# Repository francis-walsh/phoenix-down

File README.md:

# phoenix-down

Phoenix Down is a PWM-controlled hot plate that regulates the temperature of your morning coffee. A 12V 2A voltage source is regulated by a buck converter to deliver a maximum of 24W to the array of power resistors, heating the board to a specified temperature monitored by a thermistor. The design uses a schmitt trigger, astable multivibrator, and a thermistor to configure the duty cycle of the PWM.

The computer has population options for different thermistors and voltage references for configuring the thermistor voltage threshold.

Rev 1 schematic

Rev 1 TLspice simulation

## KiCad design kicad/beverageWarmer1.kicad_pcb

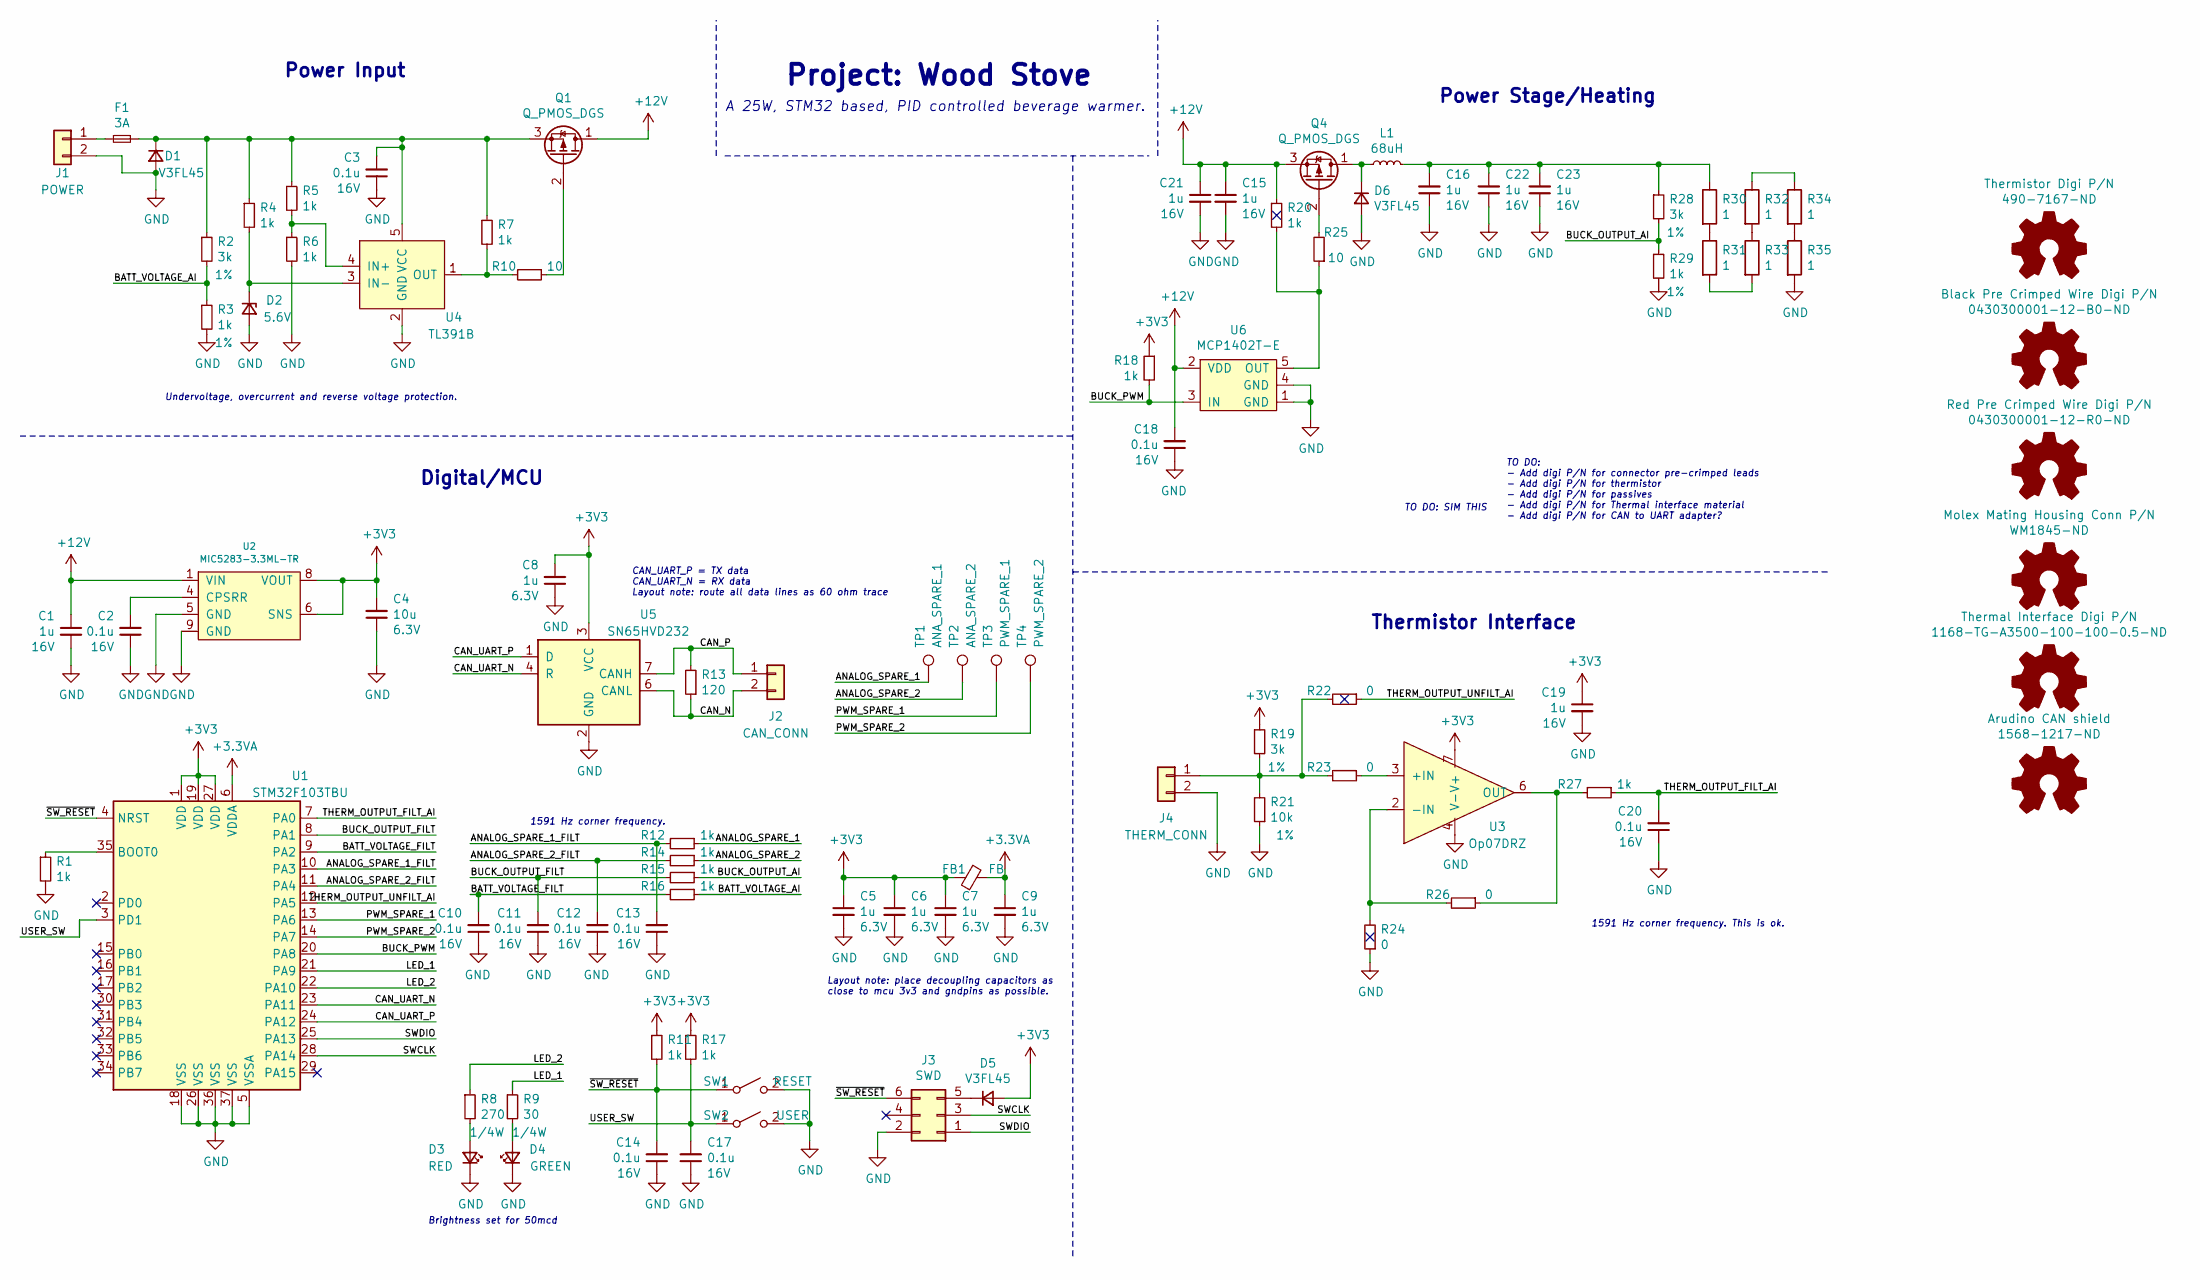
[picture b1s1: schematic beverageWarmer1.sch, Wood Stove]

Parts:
C1, C15, C16, C19, C21, C22, C23: 1u; C_0603_1608Metric; Voltage 16V; Digi 445-6931-1-ND
C2, C3, C10, C11, C12, C13, C14, C17, C18, C20: 0.1u; C_0603_1608Metric; Voltage 16V; Digi 1276-1019-1-ND
C4: 10u; C_1206_3216Metric; Voltage 6.3V; Digi 1276-6641-1-ND
C5, C6, C7, C8, C9: 1u; C_0603_1608Metric; Voltage 6.3V
D1, D5, D6: V3FL45; D_SMF; Digi V3FL45HM3/HGICT-ND
D2: 5.6V; D_SOD-123; Digi DDZ5V6BDICT-ND
D3: RED; LED_0603_1608Metric; Digi 754-1123-1-ND
D4: GREEN; LED_0603_1608Metric; Digi 754-1357-1-ND
F1: 3A; Fuse_0603_1608Metric; Digi P15118CT-ND
FB1: FB; L_0603_1608Metric; Digi 490-1015-1-ND
J1: POWER; Molex_Micro-Fit_3.0_43650-0200_1x02_P3.00mm_Horizontal; Digi WM1860-ND
J2: CAN_CONN; Molex_Micro-Fit_3.0_43650-0200_1x02_P3.00mm_Horizontal; Digi WM1860-ND
J3: SWD; PinSocket_2x03_P1.27mm_Vertical; Digi S9015E-03-ND
J4: THERM_CONN; Molex_Micro-Fit_3.0_43650-0200_1x02_P3.00mm_Horizontal; Digi WM1860-ND
L1: 68uH; L_Bourns_SRR1260; Digi SRR1260-560MCT-ND
Q1, Q4: Q_PMOS_DGS; SISS05DN-T1-GE3; Digi SISS05DN-T1-GE3CT-ND
R1, R4, R5, R6, R7, R11, R12, R14, R15, R16, R17, R18, R20, R27: 1k; R_0603_1608Metric; Digi RMCF0603JJ1K00CT-ND
R2, R19, R28: 3k; R_0603_1608Metric; Tolerance 1%; Digi RMCF0603FT3K00CT-ND
R3, R29: 1k; R_0603_1608Metric; Tolerance 1%; Digi RMCF0603FT1K00CT-ND
R8: 270; R_0805_2012Metric; Digi A130470CT-ND
R9: 30; R_0805_2012Metric; Digi 2019-RK73H2ATTD30R0FCT-ND
R10, R25: 10; R_0603_1608Metric; Digi A130079CT-ND
R13: 120; R_0603_1608Metric; Digi A129677CT-ND
R21: 10k; R_0603_1608Metric; Tolerance 1%; Digi RMCF0603FT1K00CT-ND
R22, R23, R24, R26: 0; R_0603_1608Metric; Digi 2019-RK73Z1JTTDCT-ND
R30, R32, R33, R34, R35: 1; 4320_SMD_RES; Digikey A143800CT-ND
R31: 1; 4320_SMD_RES; Digi A143800CT-ND
SW1: RESET; SW_SPST_B3U-1000P; Digi SW1020CT-ND
SW2: USER; SW_SPST_B3U-1000P; Digi SW1020CT-ND
TP1: ANA_SPARE_1; TestPoint_Pad_D1.0mm
TP2: ANA_SPARE_2; TestPoint_Pad_D1.0mm
TP3: PWM_SPARE_1; TestPoint_Pad_D1.0mm
TP4: PWM_SPARE_2; TestPoint_Pad_D1.0mm
U1: STM32F103TBU; QFN-36-1EP_6x6mm_P0.5mm_EP4.1x4.1mm; Digi 497-18758-1-ND
U2: MIC5283-3.3ML-TR; DFN-8-1EP_3x3mm_P0.65mm_EP1.55x2.4mm; Digi MIC5283-3.3YML-CT-ND
U3: Op07DRZ; SOIC-8_3.9x4.9mm_P1.27mm; Digikey OP07DRZ-ND
U4: TL391B; SOT-23-5; Digi 296-TL391BIDBVRCT-ND
U5: SN65HVD232; SOIC-8_3.9x4.9mm_P1.27mm; Digi 296-12282-5-ND
U6: MCP1402T-E; SOT-23-5; Digi MCP1402T-E/OTCT-ND

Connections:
+3.3VA: C9.1, FB1.1, U1.6 (VDDA)
+3V3: C4.2, C5.1, C6.1, C7.1, C8.2, C19.1, D5.2 (A), FB1.2, R11.1, R17.1, R18.1, R19.1, U1.1 (VDD), U1.19 (VDD), U1.27 (VDD), U2.6 (SNS), U2.8 (VOUT), U3.7 (V+), U5.3 (VCC)
+12V: C1.1, C15.1, C18.2, C21.1, Q1.1 (D), Q4.3 (S), R20.1, U2.1 (VIN), U6.2 (VDD)
/ANALOG_SPARE_1: R12.1, TP1.1
/ANALOG_SPARE_1_FILT: C13.2, R12.2, U1.10 (PA3)
/ANALOG_SPARE_2: R14.1, TP2.1
/ANALOG_SPARE_2_FILT: C12.2, R14.2, U1.11 (PA4)
/BATT_VOLTAGE_AI: R2.2, R3.1, R16.1
/BATT_VOLTAGE_FILT: C10.2, R16.2, U1.9 (PA2)
/BUCK_OUTPUT_AI: R15.1, R28.2, R29.1
/BUCK_OUTPUT_FILT: C11.2, R15.2, U1.8 (PA1)
/BUCK_PWM: R18.2, U1.20 (PA8), U6.3 (IN)
/CAN_N: J2.2, R13.1, U5.6 (CANL); also elsewhere on the board
/CAN_P: J2.1, R13.2, U5.7 (CANH); also elsewhere on the board
/CAN_UART_N: U1.23 (PA11), U5.4 (R)
/CAN_UART_P: U1.24 (PA12), U5.1 (D)
/LED_1: R9.1, U1.21 (PA9)
/LED_2: R8.1, U1.22 (PA10)
/PWM_SPARE_1: TP3.1, U1.13 (PA6)
/PWM_SPARE_2: TP4.1, U1.14 (PA7)
/SWCLK: J3.3, U1.28 (PA14); also elsewhere on the board
/SWDIO: J3.1, U1.25 (PA13); also elsewhere on the board
/THERM_OUTPUT_FILT_AI: C20.2, R27.1, U1.7 (PA0)
/THERM_OUTPUT_UNFILT_AI: R22.1, U1.12 (PA5)
/USER_SW: C17.2, R17.2, SW2.1 (A), U1.3 (PD1); also elsewhere on the board
/~SW_RESET: C14.2, J3.6, R11.2, SW1.1 (A), U1.4 (NRST); also elsewhere on the board
GND: C1.2, C2.1, C3.1, C4.1, C5.2, C6.2, C7.2, C8.1, C9.2, C10.1, C11.1, C12.1, C13.1, C14.1, C15.2, C16.1, C17.1, C18.1, C19.2, C20.1, C21.2, C22.1, C23.1, D1.2 (A), D2.2 (A), D3.1 (K), D4.1 (K), D6.2 (A), J1.2, J3.2, J4.2, R1.2, R3.2, R6.2, R21.1, R24.1, R29.2, R35.2, SW1.2 (B), SW2.2 (B), U1.5 (VSSA), U1.18 (VSS), U1.26 (VSS), U1.36 (VSS), U1.37 (VSS), U2.5 (GND), U2.9 (GND), U3.4 (V-), U4.2 (GND), U5.2 (GND), U6.1 (GND), U6.4 (GND); also elsewhere on the board
unnamed: C2.2, U2.4 (CPSRR)
unnamed: C3.2, D1.1 (K), F1.2, Q1.3 (S), R2.1, R4.1, R5.1, R7.1, U4.5 (VCC)
unnamed: C16.2, C22.2, C23.2, L1.2, R28.1, R30.1
unnamed: D2.1 (K), R4.2, U4.3 (IN-)
unnamed: D3.2 (A), R8.2
unnamed: D4.2 (A), R9.2
unnamed 33: D5.1 (K), J3.5; also elsewhere on the board
unnamed: D6.1 (K), L1.1, Q4.1 (D)
unnamed 35: F1.1, J1.1; also elsewhere on the board
unnamed 37: J4.1, R19.2, R21.2, R22.2, R23.2; also elsewhere on the board
unnamed: Q1.2 (G), R10.1
unnamed: Q4.2 (G), R25.2
unnamed: R1.1, U1.35 (BOOT0)
unnamed: R5.2, R6.1, U4.4 (IN+)
unnamed: R7.2, R10.2, U4.1 (OUT)
unnamed: R20.2, R25.1, U6.5 (OUT)
unnamed: R23.1, U3.3 (+IN)
unnamed: R24.2, R26.2, U3.2 (-IN)
unnamed: R26.1, R27.2, U3.6 (OUT)
unnamed: R30.2, R31.1
unnamed: R31.2, R33.2
unnamed: R32.1, R34.1
unnamed: R32.2, R33.1
unnamed: R34.2, R35.1

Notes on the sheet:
Layout note: place decoupling capacitors as close to mcu 3v3 and gndpins as possible.
TO DO: SIM THIS
1591 Hz corner frequency. This is ok.
Undervoltage, overcurrent and reverse voltage protection.
Thermistor Interface
Digital/MCU
Power Input
Power Stage/Heating
Project: Wood Stove
A 25W, STM32 based, PID controlled beverage warmer.
CAN_UART_P = TX data CAN_UART_N = RX data Layout note: route all data lines as 60 ohm trace
TO DO: - Add digi P/N for connector pre-crimped leads - Add digi P/N for thermistor - Add digi P/N for passives - Add digi P/N for Thermal interface material - Add digi P/N for CAN to UART adapter?
1591 Hz corner frequency.
Brightness set for 50mcd

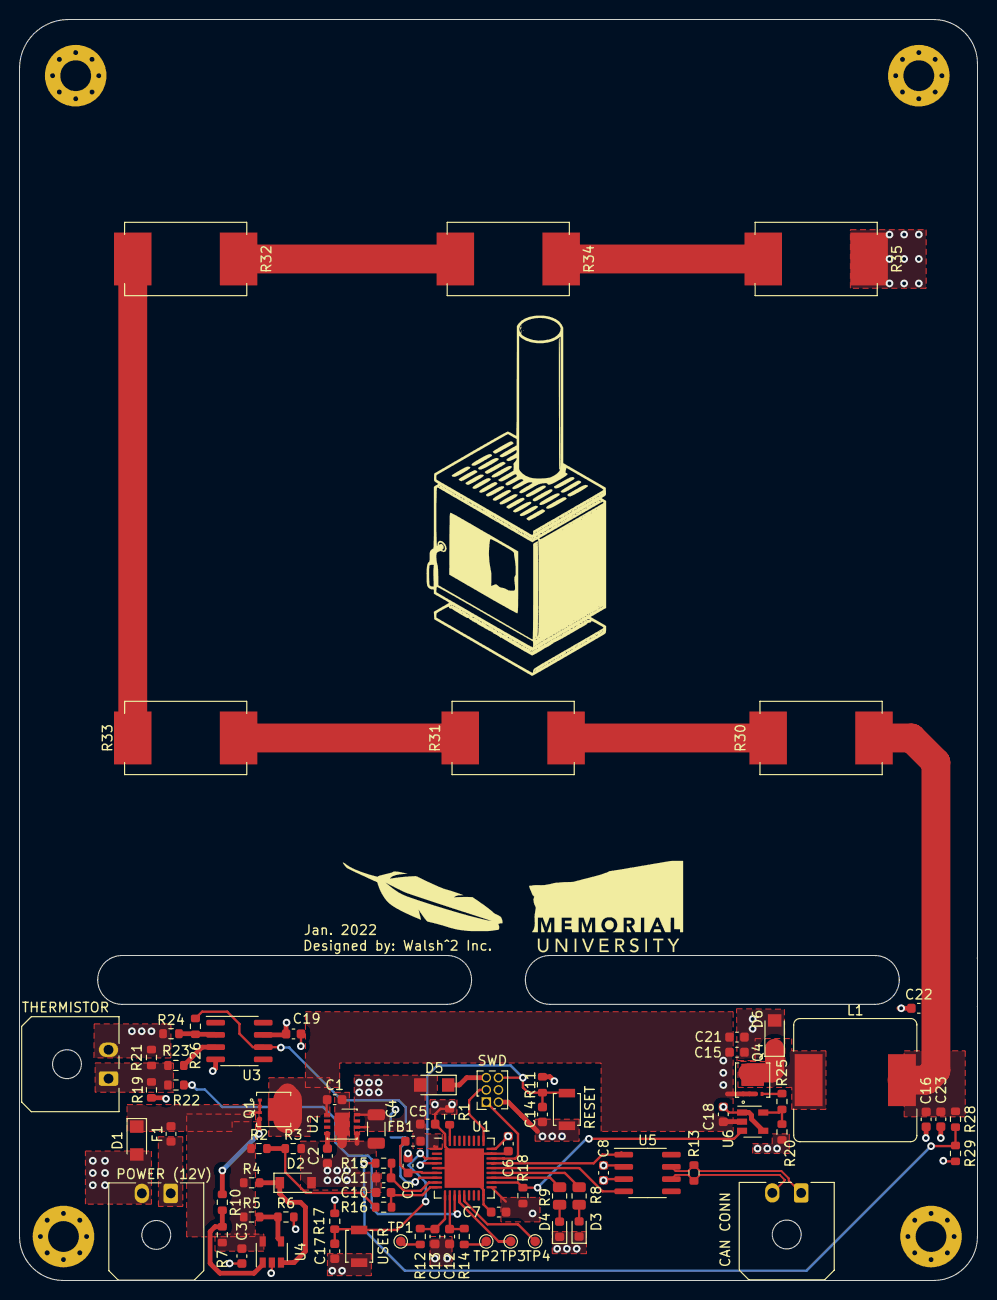
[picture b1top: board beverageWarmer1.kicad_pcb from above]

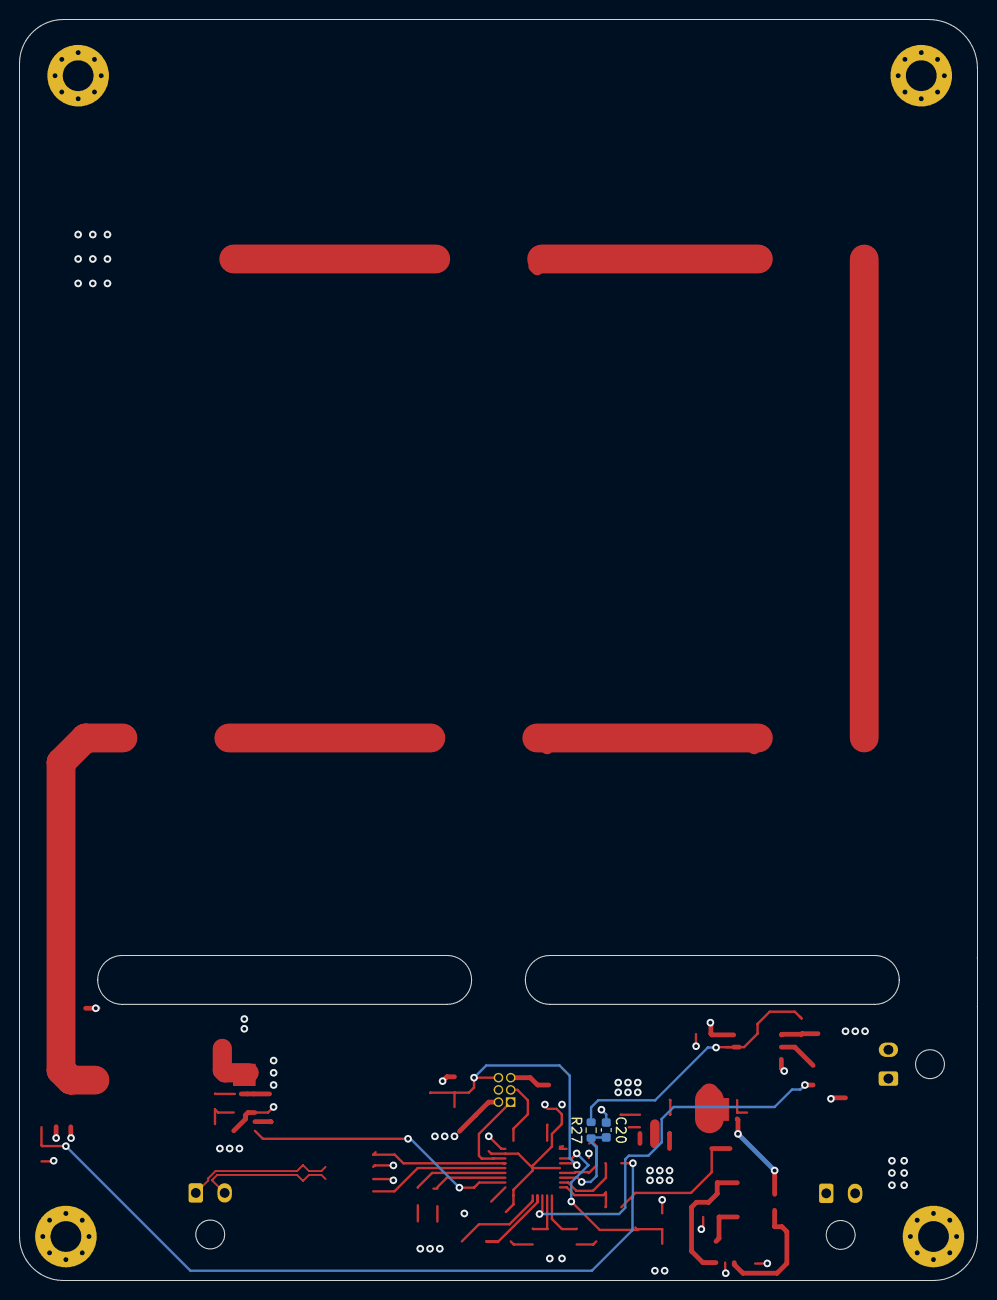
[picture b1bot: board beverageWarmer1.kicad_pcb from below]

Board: 4 copper layers, 99.6 x 131.1 mm, 85 parts (2 on the bottom side), 51 nets.

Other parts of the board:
CAN CONN: CAN_CONN; Molex_Micro-Fit_3.0_43650-0200_1x02_P3.00mm_Horizontal
POWER (12V): POWER; Molex_Micro-Fit_3.0_43650-0200_1x02_P3.00mm_Horizontal
RESET: RESET; SW_SPST_B3U-1000P
SWD: SWD; PinSocket_2x03_P1.27mm_Vertical
THERMISTOR: THERM_CONN; Molex_Micro-Fit_3.0_43650-0200_1x02_P3.00mm_Horizontal
USER: USER; SW_SPST_B3U-1000P

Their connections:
/CAN_N: CAN CONN.2; also elsewhere on the board
/CAN_P: CAN CONN.1; also elsewhere on the board
/SWCLK: SWD.3; also elsewhere on the board
/SWDIO: SWD.1; also elsewhere on the board
/USER_SW: USER.1; also elsewhere on the board
/~SW_RESET: RESET.1, SWD.6; also elsewhere on the board
GND: POWER (12V).2, RESET.2, SWD.2, THERMISTOR.2, USER.2; also elsewhere on the board
unnamed 33: SWD.5; also elsewhere on the board
unnamed 35: POWER (12V).1; also elsewhere on the board
unnamed 37: THERMISTOR.1; also elsewhere on the board

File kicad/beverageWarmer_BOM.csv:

Item,Qty,Reference(s),Value,Digi,Have,Power,Tolerance,Voltage
1,30,"C1, C5, C6, C7, C8, C9, C15, C16, C19",1u,445-6931-1-ND,,,,16V
2,25,"C2, C3, C10, C11, C12, C13, C14, C17, C18, C20",0.1u,1276-1019-1-ND,,,,16V
3,5,C4,10u,1276-6641-1-ND,,,,6.3V
4,10,"D1, D5, D6",V3FL45,V3FL45HM3/HGICT-ND,,,,
5,4,D2,5.6V,DDZ5V6BDICT-ND,,,,
6,4,D3,RED,754-1123-1-ND,,,,
7,4,D4,GREEN,754-1357-1-ND,,,,
8,10,F1,3A,P15118CT-ND,,,,
9,4,FB1,FB,490-1015-1-ND,,,,
10,2,J1,POWER,WM1860-ND,,,,
11,2,J2,CAN_CONN,WM1860-ND,,,,
12,3,J3,SWD,S9015E-03-ND,,,,
13,1,J4,THERM_CONN,WM1860-ND,,,,
14,3,L1,68uH,SRR1260-560MCT-ND,,,,
15,9,"Q1, Q4",Q_PMOS_DGS,SISS05DN-T1-GE3CT-ND,,,,
16,40,"R1, R3, R4, R5, R6, R7, R11, R12, R14, R15, R16, R17, R18, R20, R27, R29",1k,RMCF0603JJ1K00CT-ND,,,1%,
17,10,"R2, R19, R28",3k,RMCF0603FT3K00CT-ND,,,1%,
18,10,R8,270,A130470CT-ND,,1/4W,,
19,10,R9,30,2019-RK73H2ATTD30R0FCT-ND,,1/4W,,
20,10,"R10, R25",10,A130079CT-ND,,,,
21,10,R13,120,A129677CT-ND,,,,
22,10,R21,10k,RMCF0603FT1K00CT-ND,,,1%,
23,10,"R22, R23, R24, R26",0,2019-RK73Z1JTTDCT-ND,,,,
24,20,"R30, R31, R32, R33, R34, R35",1,A143800CT-ND,,,,
25,2,SW1,RESET,SW1020CT-ND,,,,
26,2,SW2,USER,SW1020CT-ND,,,,
27,3,U1,STM32F103TBU,497-18758-1-ND,Yes,,,
28,3,U2,MIC5283-3.3ML-TR,MIC5283-3.3YML-CT-ND,Yes,,,
29,5,U3,Op07DRZ,OP07DRZ-ND,Yes,,,
30,10,U4,TL391B,296-TL391BIDBVRCT-ND,,,,
31,3,U5,SN65HVD232,296-12282-5-ND,Yes,,,
32,10,U6,MCP1402T-E,MCP1402T-E/OTCT-ND,,,,

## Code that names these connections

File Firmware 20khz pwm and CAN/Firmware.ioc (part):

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Mcu.Name=STM32F103T(8-B)Ux
Mcu.Package=VFQFPN36
Mcu.UserName=STM32F103TBUx
PA0-WKUP.GPIOParameters=GPIO_Label
PA0-WKUP.GPIO_Label=THERM_FILT_AI
PA0-WKUP.Signal=ADCx_IN0
PA1.GPIOParameters=GPIO_Label
PA1.GPIO_Label=BUCK_OUTPUT_FILT
PA1.Signal=ADCx_IN1
PA10.GPIOParameters=GPIO_Label
PA10.GPIO_Label=LED_2
PA10.Signal=GPIO_Output
PA11.Mode=CAN_Activate
PA11.Signal=CAN_RX
PA12.Mode=CAN_Activate
PA12.Signal=CAN_TX
PA13.Mode=Serial_Wire
PA13.Signal=SYS_JTMS-SWDIO
PA14.Mode=Serial_Wire
PA14.Signal=SYS_JTCK-SWCLK
PA2.GPIOParameters=GPIO_Label
PA2.GPIO_Label=BATT_VOLTAGE_FILT
PA2.Signal=ADCx_IN2
PA8.GPIOParameters=GPIO_Label
PA8.GPIO_Label=BUCK_PWM
PA8.Signal=S_TIM1_CH1
PA9.GPIOParameters=GPIO_Label
PA9.GPIO_Label=LED_1
PA9.Signal=GPIO_Output
PD1-OSC_OUT.GPIOParameters=GPIO_PuPd,GPIO_Label,GPIO_ModeDefaultEXTI
PD1-OSC_OUT.GPIO_Label=USER_PB
PD1-OSC_OUT.GPIO_ModeDefaultEXTI=GPIO_MODE_IT_FALLING
PD1-OSC_OUT.GPIO_PuPd=GPIO_NOPULL
PD1-OSC_OUT.Signal=GPXTI1
board=custom

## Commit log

2021-05-10 Init Commit
2021-05-11 Added photos of schematic
2021-05-17 Fixed Spelling Mistake
2021-05-22 Added PCBA image
2022-01-13 first push
2022-01-14 2nd commit
    changed gate drive for buck converter
2022-01-14 Final Sch Push?
2022-01-15 Preliminary Layout Complete
2022-01-17 Finished Layout
2022-01-17 Adjusted Silk Screen
2022-01-17 small ss and copper changes
2022-01-18 Hopefully the ordered gerbers
2022-02-21 firstTryPWM
2022-02-21 Added HMI python script
2022-02-22 Added more functions to python script, and added arduino firmware
2022-02-24 daniel's broken temp set... probably just a binary formatting issue
    ... probably just a binary formatting issue

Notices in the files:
parts and their libraries:
Copyright 2021 Accelerated Designs. All rights reserved.
